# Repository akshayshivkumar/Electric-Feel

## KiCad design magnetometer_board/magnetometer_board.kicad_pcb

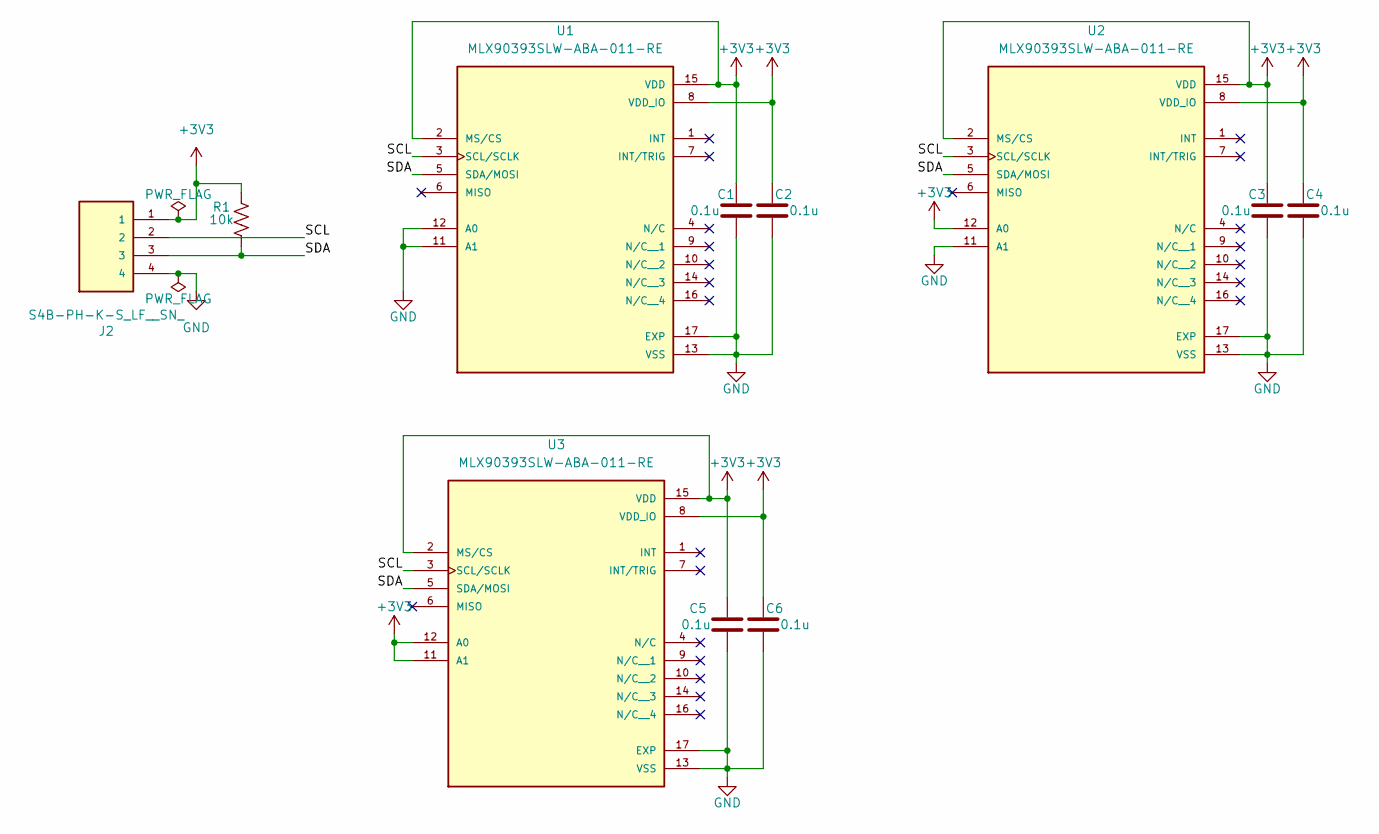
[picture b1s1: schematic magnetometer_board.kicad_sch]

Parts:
C1, C2, C3, C4, C5, C6: 0.1u; C_0603_1608Metric
J2: S4B-PH-K-S_LF__SN_; JST_S4B-PH-K-S_LF__SN_
R1: 10k; R_0603_1608Metric
U1, U2, U3: MLX90393SLW-ABA-011-RE; QFN50P300X300X100-17N; PARTREV 010

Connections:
+3V3: C1.1, C2.1, C3.1, C4.1, C5.1, C6.1, J2.1, R1.2, U1.2 (MS/CS), U1.8 (VDD_IO), U1.15 (VDD), U2.2 (MS/CS), U2.8 (VDD_IO), U2.12 (A0), U2.15 (VDD), U3.2 (MS/CS), U3.8 (VDD_IO), U3.11 (A1), U3.12 (A0), U3.15 (VDD)
/SCL: J2.2, U1.3 (SCL/SCLK), U2.3 (SCL/SCLK), U3.3 (SCL/SCLK)
/SDA: J2.3, R1.1, U1.5 (SDA/MOSI), U2.5 (SDA/MOSI), U3.5 (SDA/MOSI)
GND: C1.2, C2.2, C3.2, C4.2, C5.2, C6.2, J2.4, U1.11 (A1), U1.12 (A0), U1.13 (VSS), U1.17 (EXP), U2.11 (A1), U2.13 (VSS), U2.17 (EXP), U3.13 (VSS), U3.17 (EXP)

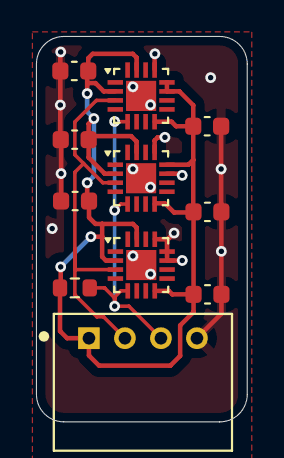
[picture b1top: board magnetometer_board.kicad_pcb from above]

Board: 2 copper layers, 11.7 x 21.4 mm, 11 parts (0 on the bottom side), 4 nets.

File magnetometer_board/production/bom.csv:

Designator,Footprint,Quantity,Value,LCSC Part #
"C1, C2, C3, C4, C5, C6",0603,6,0.1u,
J2,JST_S4B-PH-K-S_LF__SN_,1,S4B-PH-K-S_LF__SN_,
R1,0603,1,10k,
"U1, U2, U3",QFN50P300X300X100-17N,3,MLX90393SLW-ABA-011-RE,

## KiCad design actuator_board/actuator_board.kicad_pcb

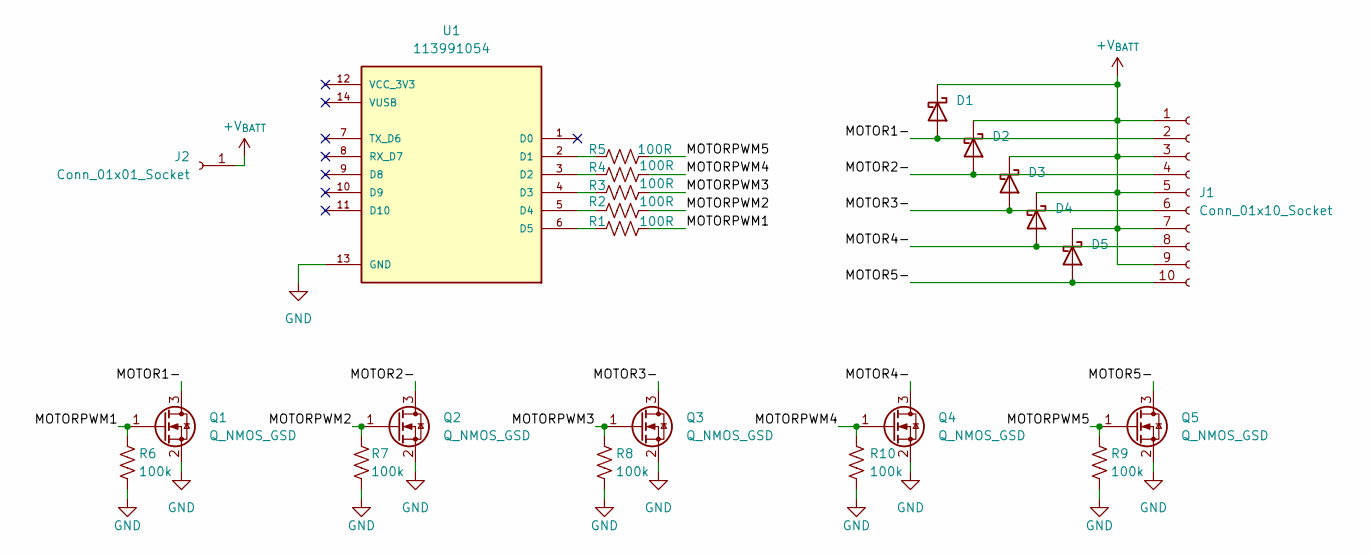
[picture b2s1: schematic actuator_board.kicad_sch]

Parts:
D1, D2, D3, D4, D5: D_Schottky; DIO_PMEG3020EH_115
J1: Conn_01x10_Socket; PinSocket_1x10_P2.54mm_Vertical
J2: Conn_01x01_Socket; PinSocket_1x01_P2.54mm_Vertical
Q1, Q2, Q3, Q4, Q5: Q_NMOS_GSD; TRANS_IRLML6344TRPBF
R1, R2, R3, R4, R5: 100R; R_0805_2012Metric_Pad1.20x1.40mm_HandSolder
R6, R7, R8, R9, R10: 100k; R_0805_2012Metric_Pad1.20x1.40mm_HandSolder
U1: 113991054; MODULE_113991054; PARTREV 23/05/2022

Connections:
+V_{BATT}: D1.1 (K), D2.1 (K), D3.1 (K), D4.1 (K), D5.1 (K), J1.1, J1.3, J1.5, J1.7, J1.9, J2.1
/MOTOR1-: D1.2 (A), J1.2, Q1.3 (D)
/MOTOR2-: D2.2 (A), J1.4, Q2.3 (D)
/MOTOR3-: D3.2 (A), J1.6, Q3.3 (D)
/MOTOR4-: D4.2 (A), J1.8, Q4.3 (D)
/MOTOR5-: D5.2 (A), J1.10, Q5.3 (D)
/MOTORPWM1: Q1.1 (G), R1.2, R6.1
/MOTORPWM2: Q2.1 (G), R2.2, R7.1
/MOTORPWM3: Q3.1 (G), R3.2, R8.1
/MOTORPWM4: Q4.1 (G), R4.2, R10.1
/MOTORPWM5: Q5.1 (G), R5.2, R9.1
GND: Q1.2 (S), Q2.2 (S), Q3.2 (S), Q4.2 (S), Q5.2 (S), R6.2, R7.2, R8.2, R9.2, R10.2, U1.13 (GND)
unnamed: R5.1, U1.2 (D1)
unnamed: R4.1, U1.3 (D2)
unnamed: R3.1, U1.4 (D3)
unnamed: R2.1, U1.5 (D4)
unnamed: R1.1, U1.6 (D5)

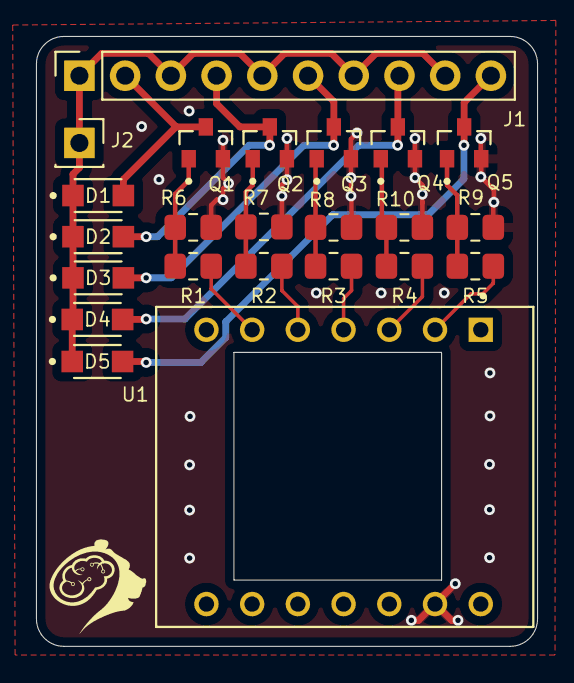
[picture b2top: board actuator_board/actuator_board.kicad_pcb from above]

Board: 2 copper layers, 27.8 x 33.9 mm, 23 parts (0 on the bottom side), 17 nets.

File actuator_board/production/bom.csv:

Designator,Footprint,Quantity,Value,LCSC Part #
"D1, D2, D3, D4, D5",DIO_PMEG3020EH_115,5,D_Schottky,
J1,PinSocket_1x10_P2.54mm_Vertical,1,Conn_01x10_Socket,
J2,PinSocket_1x01_P2.54mm_Vertical,1,Conn_01x01_Socket,
"Q1, Q2, Q3, Q4, Q5",TRANS_IRLML6344TRPBF,5,Q_NMOS_GSD,
"R1, R2, R3, R4, R5",0805,5,100R,
"R10, R6, R7, R8, R9",0805,5,100k,
U1,MODULE_113991054,1,113991054,

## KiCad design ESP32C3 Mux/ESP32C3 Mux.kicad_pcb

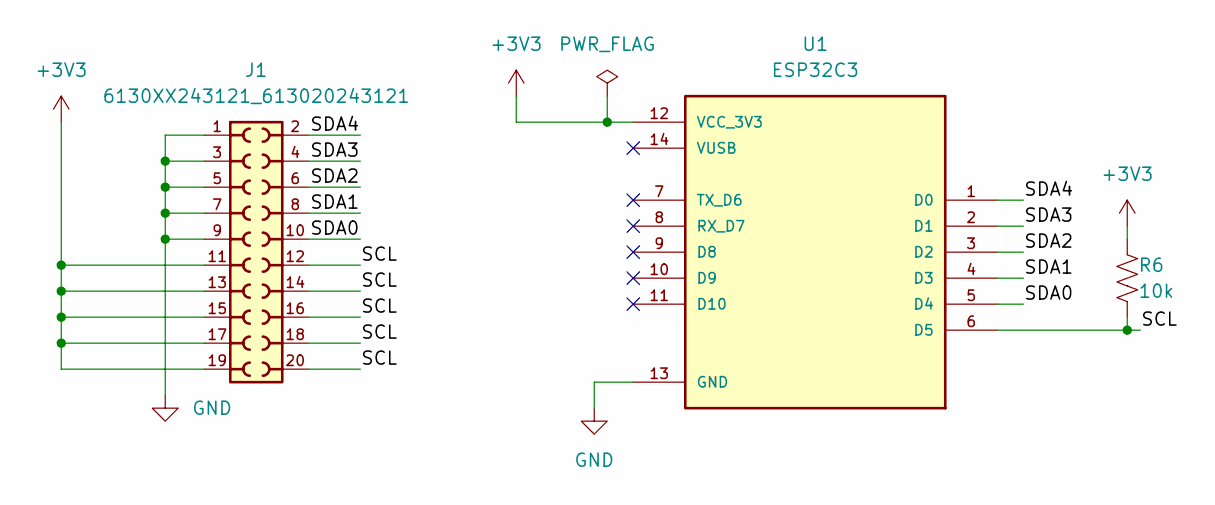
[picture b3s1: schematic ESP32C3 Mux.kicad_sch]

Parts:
J1: 6130XX243121_613020243121; 613020243121
R6: 10k; R_0603_1608Metric_Pad0.98x0.95mm_HandSolder
U1: ESP32C3; PARTREV 23/05/2022

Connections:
+3V3: J1.11, J1.13, J1.15, J1.17, J1.19, R6.1, U1.12 (VCC_3V3)
/SCL: J1.12, J1.14, J1.16, J1.18, J1.20, R6.2, U1.6 (D5)
/SDA0: J1.10, U1.5 (D4)
/SDA1: J1.8, U1.4 (D3)
/SDA2: J1.6, U1.3 (D2)
/SDA3: J1.4, U1.2 (D1)
/SDA4: J1.2, U1.1 (D0)
GND: J1.1, J1.3, J1.5, J1.7, J1.9, U1.13 (GND)

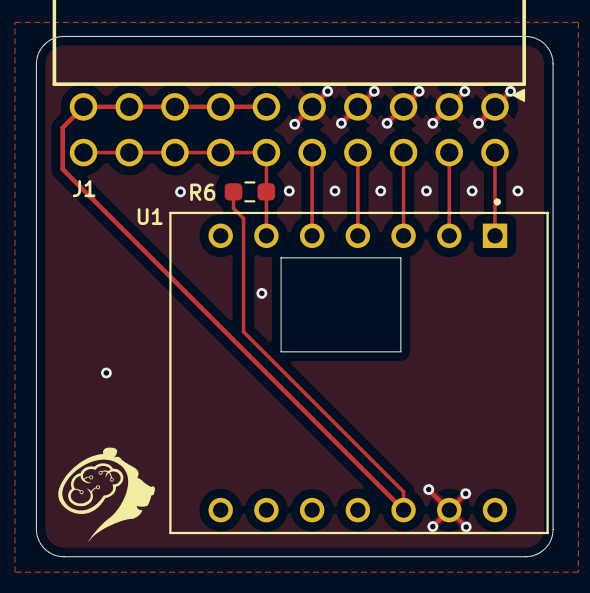
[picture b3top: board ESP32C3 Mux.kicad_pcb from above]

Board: 2 copper layers, 28.7 x 28.9 mm, 3 parts (0 on the bottom side), 8 nets.

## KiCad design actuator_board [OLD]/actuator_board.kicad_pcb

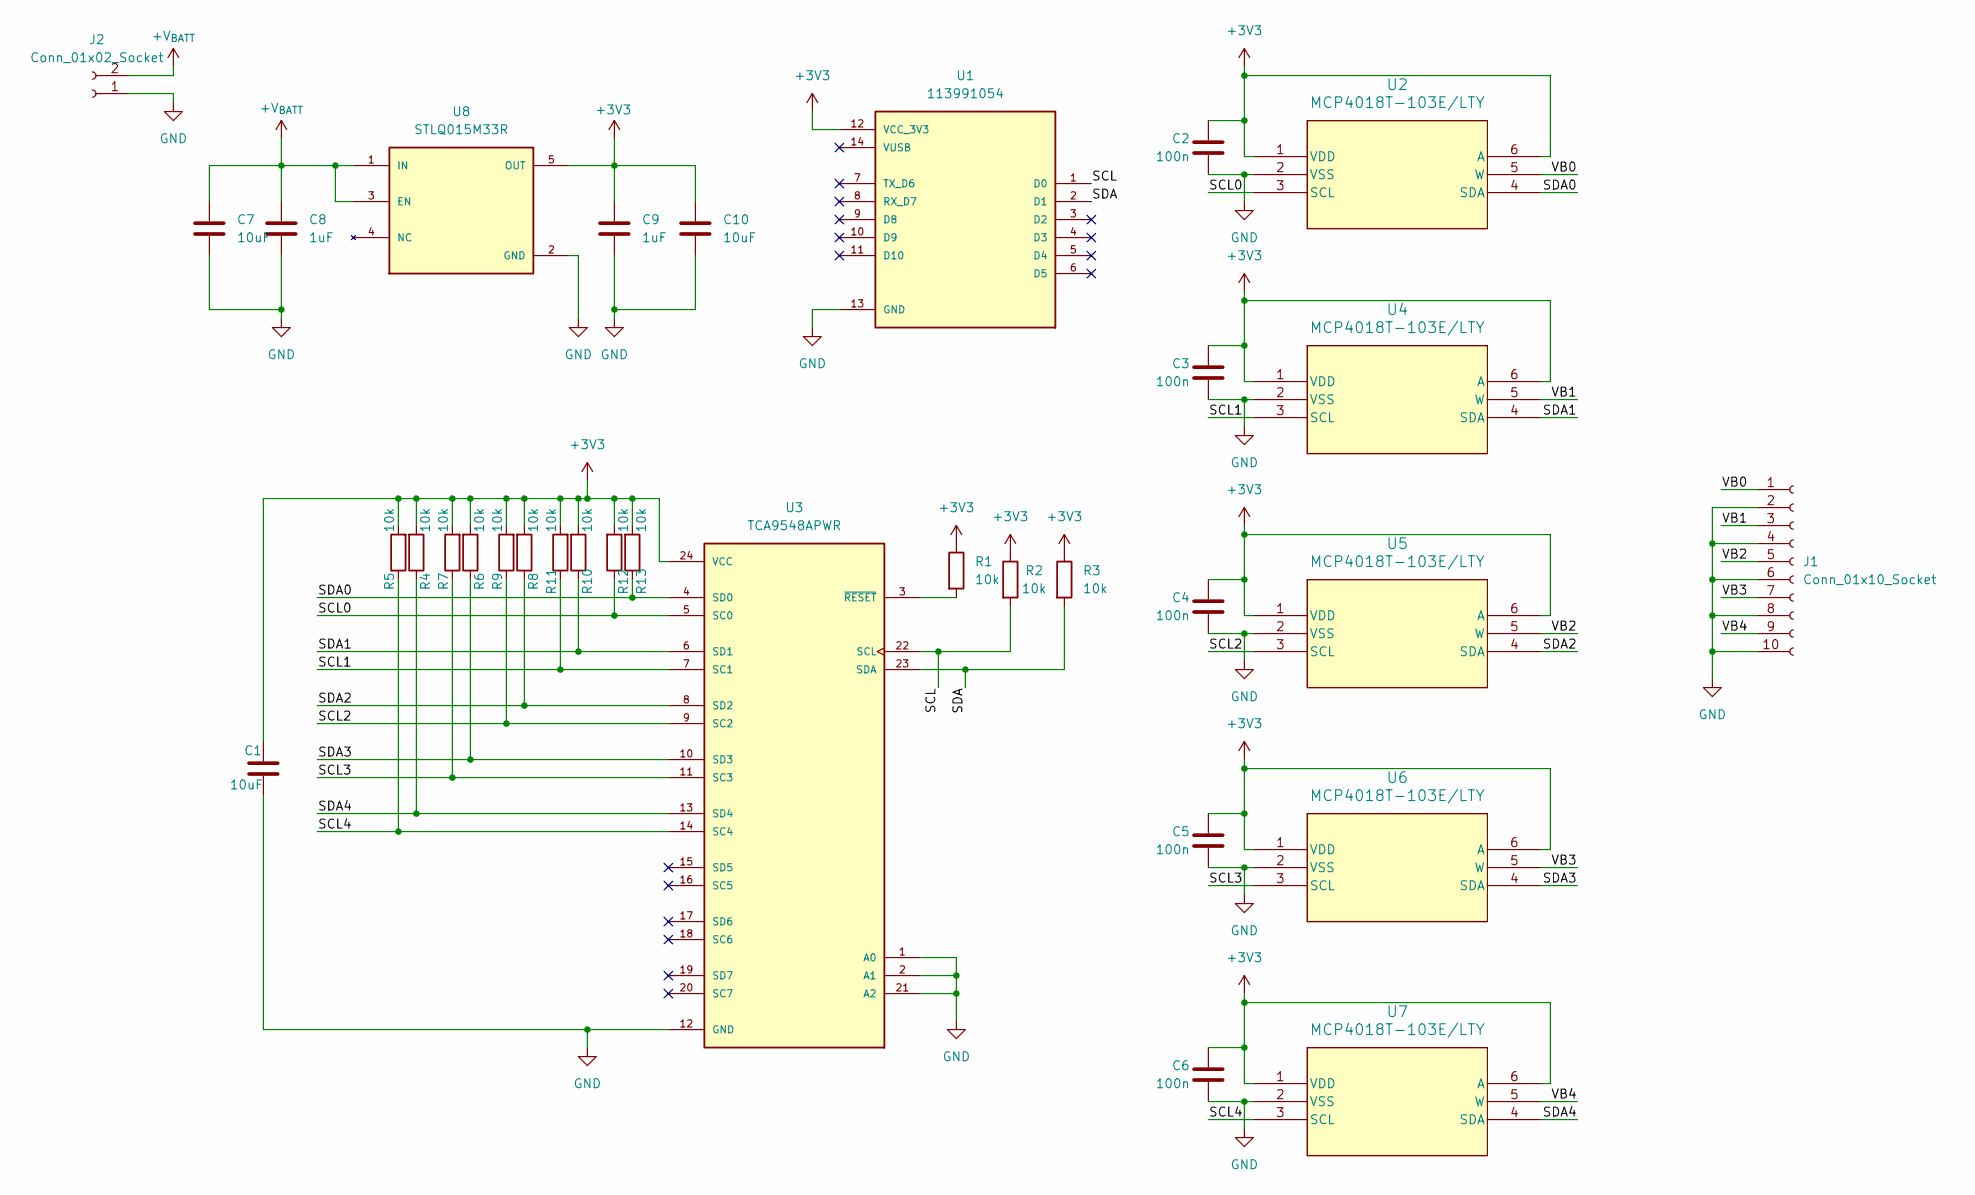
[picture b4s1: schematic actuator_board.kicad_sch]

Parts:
C1, C7, C10: 10uF; C_0805_2012Metric
C2, C3, C4, C5, C6: 100n; C_0805_2012Metric
C8, C9: 1uF; C_0805_2012Metric
J1: Conn_01x10_Socket; PinSocket_1x10_P1.00mm_Vertical
J2: Conn_01x02_Socket; JST_PH_B2B-PH-K_1x02_P2.00mm_Vertical
R1, R2, R3, R4, R5, R6, R7, R8, R9, R10, R11, R12, R13: 10k; R_0805_2012Metric
U1: 113991054; MODULE_113991054; PARTREV 23/05/2022
U2, U4, U5, U6, U7: MCP4018T-103E/LTY; SC70-6_LT_MCH
U3: TCA9548APWR; SOP65P640X120-24N; PARTREV G
U8: STLQ015M33R; SOT95P280X145-5N; PARTREV 7

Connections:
+3V3: C1.1, C2.2, C3.2, C4.2, C5.2, C6.2, C9.1, C10.1, R1.1, R2.1, R3.1, R4.2, R5.2, R6.2, R7.2, R8.2, R9.2, R10.2, R11.2, R12.2, R13.2, U1.12 (VCC_3V3), U2.1 (VDD), U2.6 (A), U3.24 (VCC), U4.1 (VDD), U4.6 (A), U5.1 (VDD), U5.6 (A), U6.1 (VDD), U6.6 (A), U7.1 (VDD), U7.6 (A), U8.5 (OUT)
+V_{BATT}: C7.1, C8.1, J2.2, U8.1 (IN), U8.3 (EN)
/SCL: R2.2, U1.1 (D0), U3.22 (SCL)
/SCL0: R12.1, U2.3 (SCL), U3.5 (SC0)
/SCL1: R11.1, U3.7 (SC1), U4.3 (SCL)
/SCL2: R9.1, U3.9 (SC2), U5.3 (SCL)
/SCL3: R7.1, U3.11 (SC3), U6.3 (SCL)
/SCL4: R5.1, U3.14 (SC4), U7.3 (SCL)
/SDA: R3.2, U1.2 (D1), U3.23 (SDA)
/SDA0: R13.1, U2.4 (SDA), U3.4 (SD0)
/SDA1: R10.1, U3.6 (SD1), U4.4 (SDA)
/SDA2: R8.1, U3.8 (SD2), U5.4 (SDA)
/SDA3: R6.1, U3.10 (SD3), U6.4 (SDA)
/SDA4: R4.1, U3.13 (SD4), U7.4 (SDA)
/VB0: J1.1, U2.5 (W)
/VB1: J1.3, U4.5 (W)
/VB2: J1.5, U5.5 (W)
/VB3: J1.7, U6.5 (W)
/VB4: J1.9, U7.5 (W)
GND: C1.2, C2.1, C3.1, C4.1, C5.1, C6.1, C7.2, C8.2, C9.2, C10.2, J1.2, J1.4, J1.6, J1.8, J1.10, J2.1, U1.13 (GND), U2.2 (VSS), U3.1 (A0), U3.2 (A1), U3.12 (GND), U3.21 (A2), U4.2 (VSS), U5.2 (VSS), U6.2 (VSS), U7.2 (VSS), U8.2 (GND)
unnamed: R1.2, U3.3 (~RESET)

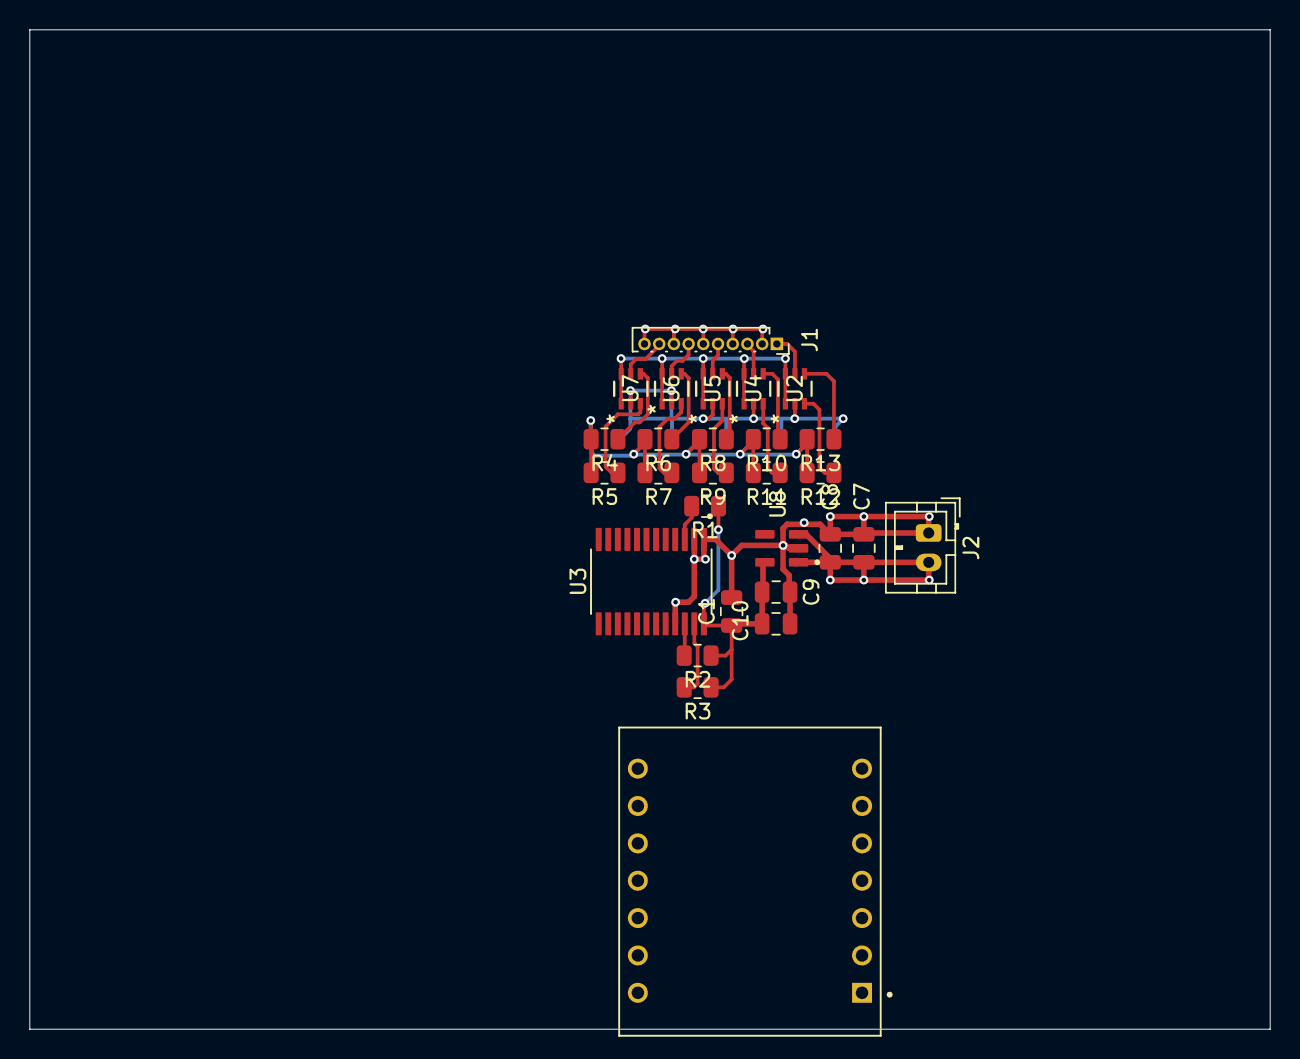
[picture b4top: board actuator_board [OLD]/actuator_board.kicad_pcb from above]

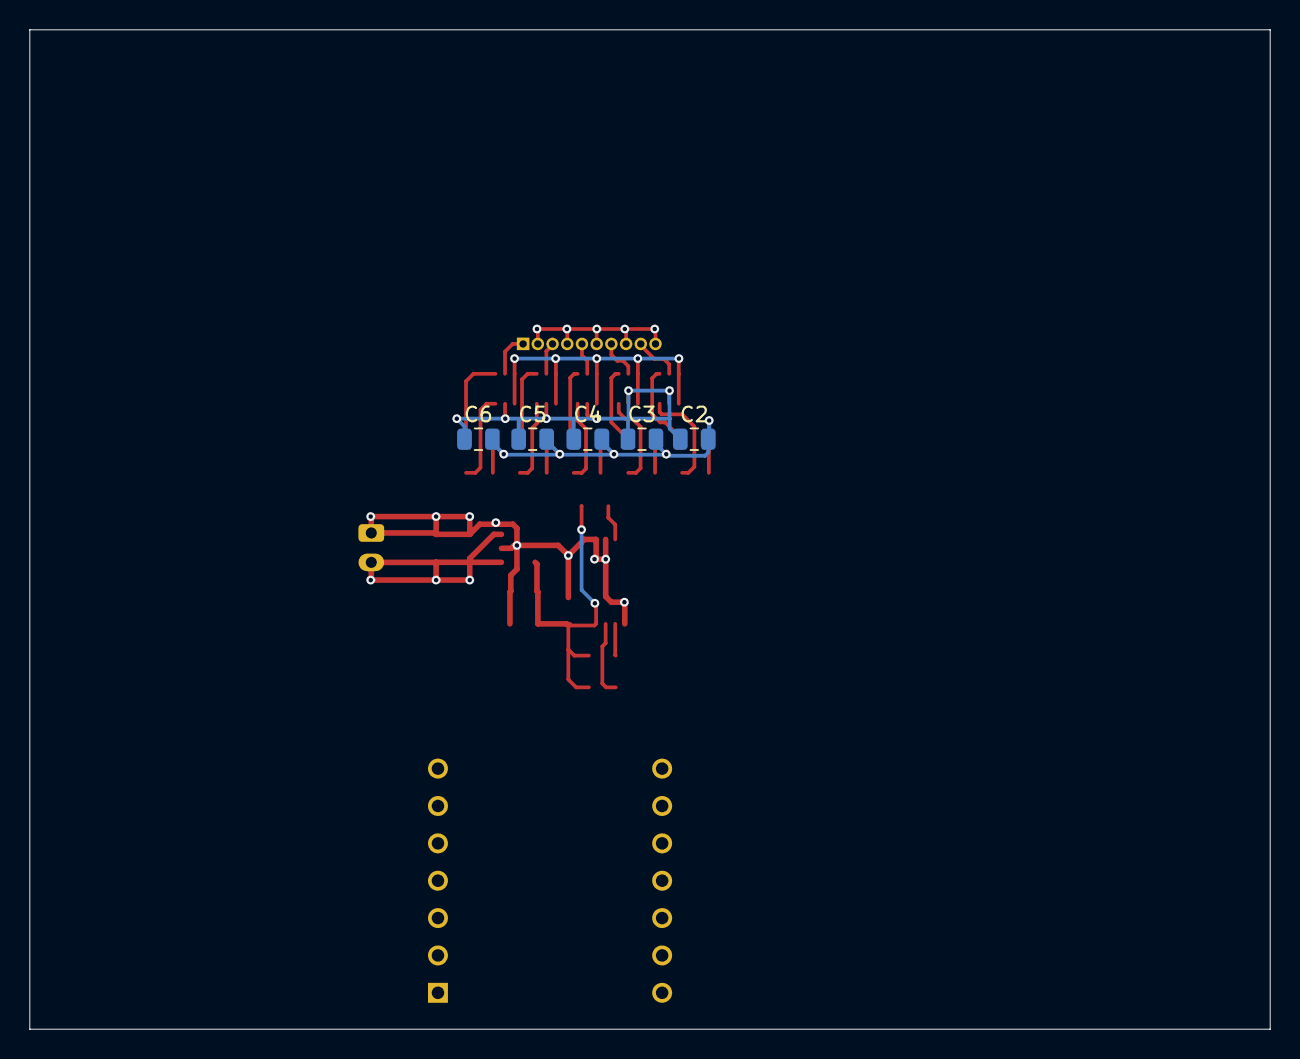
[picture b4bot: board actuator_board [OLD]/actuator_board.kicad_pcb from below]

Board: 2 copper layers, 84.3 x 67.9 mm, 33 parts (5 on the bottom side), 21 nets.

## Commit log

2025-10-19 Added magnetometer pcb.
2025-10-19 started esp32 + mux schematic
2025-10-21 finished esp32 mux schematic
2025-10-21 Finished actuator board draft.
2025-10-21 fixed power flag errors
2025-10-21 forgot to save kicad file lol
2025-11-02 Actuator board schematic done
2025-11-03 start layout for sensor control
2025-11-04 finished layout
2025-11-04 drc errors
2025-11-04 cleaned up some traces
2025-11-05 Finished actuator board.
2025-11-09 removed mux and added 2 2x8 pin headers
2025-11-11 Fixed actuator board and revised magnetometer board
2025-11-12 Re-layout of sensor control board
2025-11-12 Final drafts for design review
2025-11-12 Fixed battery issues, removed LDOs
2025-12-03 Final version
2025-12-05 YEEEEEEEEEEEEEEEEEEESSSSSSSSSSSSS
2025-12-05 magne
2025-12-07 firmware
